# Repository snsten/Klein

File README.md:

# Klein Keyboard

Klein keyboard is a 36 keys, columnar staggered, split keyboard named after [Felix Klein](https://en.wikipedia.org/wiki/Felix_Klein)

---

## Features

- Column Staggered
- Bluetooth compatible with power switch
- Seeed Studio XIAO-BLE / Pro Micro / nice!nano\* / KB2040 / RP2040(boards with Pro Micro pinout) compatible
- Hotswap MX and Choc switches support
- Trackpad support with FPC cable and direct wiring
- Reversible SMD and through hole diode footprint

> \* nice!nano firmware not available at the moment.

## Versions

Supports multiple options of micro controller and sensors.

| Features Supported                       | Microcontroller | Firmware available                         | Wired | Wireless |
| ---------------------------------------- | --------------- | ------------------------------------------ | ----- | -------- |
| Encoder or OLED                          | XIAO-BLE        | [Yes](https://github.com/snsten/Klein-zmk) |       | Yes      |
| Encoder, OLED, TouchPad, Buzzer, Haptics | Pro Micro       | [Yes](https://github.com/snsten/Klein-qmk) | Yes   |          |
| Encoder, OLED, TouchPad, Buzzer, Haptics | KB2040/RP2040   | [Yes](https://github.com/snsten/Klein-qmk) | Yes   |          |
| Encoder and OLED                         | nice!nano       | No (Planned)                               |       | Yes      |

Broadly divided in two types:

### Wireless

- Can be made with Seeed Studio XIAO-BLE
- Supports either rotary encoder or OLED
- Battery connectors JST and THT

Wireless touchpad is currently not supported in ZMK.

### Wired

- With any Pro Micro based boards
  - Can support encoders, OLED, Touchpad, Buzzer and Haptics

---

### Keyboard Images

PCB with both Choc and MX switches

Low Profile Choc version

MX version

---

## Repo Layout and Files

```
.
├── BOM
│   ├── BOM-3235-SEEED.csv         <- BOM
│   └── ibom.html
├── Case
│   └── *.stl                      <- Case stl Files
│   └── Prototype                  <- FreeCad project files (Not tested)
│       └── SwitchPlateFR4         <- SwitchPlate PCB files (Not tested)
├── docs
│   └── images
├── Logo
├── PCB
└── README.md
```

## BOM

It is available in BOM directory as csv file and [interactive HTML BOM](https://htmlpreview.github.io/?https://github.com/snsten/Klein/blob/main/BOM/ibom.html)

## Build Guide

- Wired build [guide](https://github.com/snsten/Klein/blob/main/docs/buildguides/buildguide_wired.md)
- Wireless build [guide](https://github.com/snsten/Klein/blob/main/docs/buildguides/buildguide_wireless.md)

## Todo

- Add Build Guide
- Add Touchpad related 3D Models
- Software support for Touchpad/OLED

## Firmware

- [ZMK shield](https://github.com/snsten/Klein-zmk) for Klein with rotary encoder support.
- [QMK Firmware](https://github.com/snsten/Klein-qmk) for Pro Micro with touchpad support.

## Refrences

These projects inspired and helped in making Klein:

- [Lily58](https://github.com/kata0510/Lily58) (Hotswap Footprints)
- [Dilemma](https://github.com/Bastardkb/dilemma) (Trackpad Mount, Design)
- [KLOR](https://github.com/GEIGEIGEIST/KLOR) (Haptics Footprints, Design)
- [Claw44](https://github.com/yfuku/claw44) (Design)

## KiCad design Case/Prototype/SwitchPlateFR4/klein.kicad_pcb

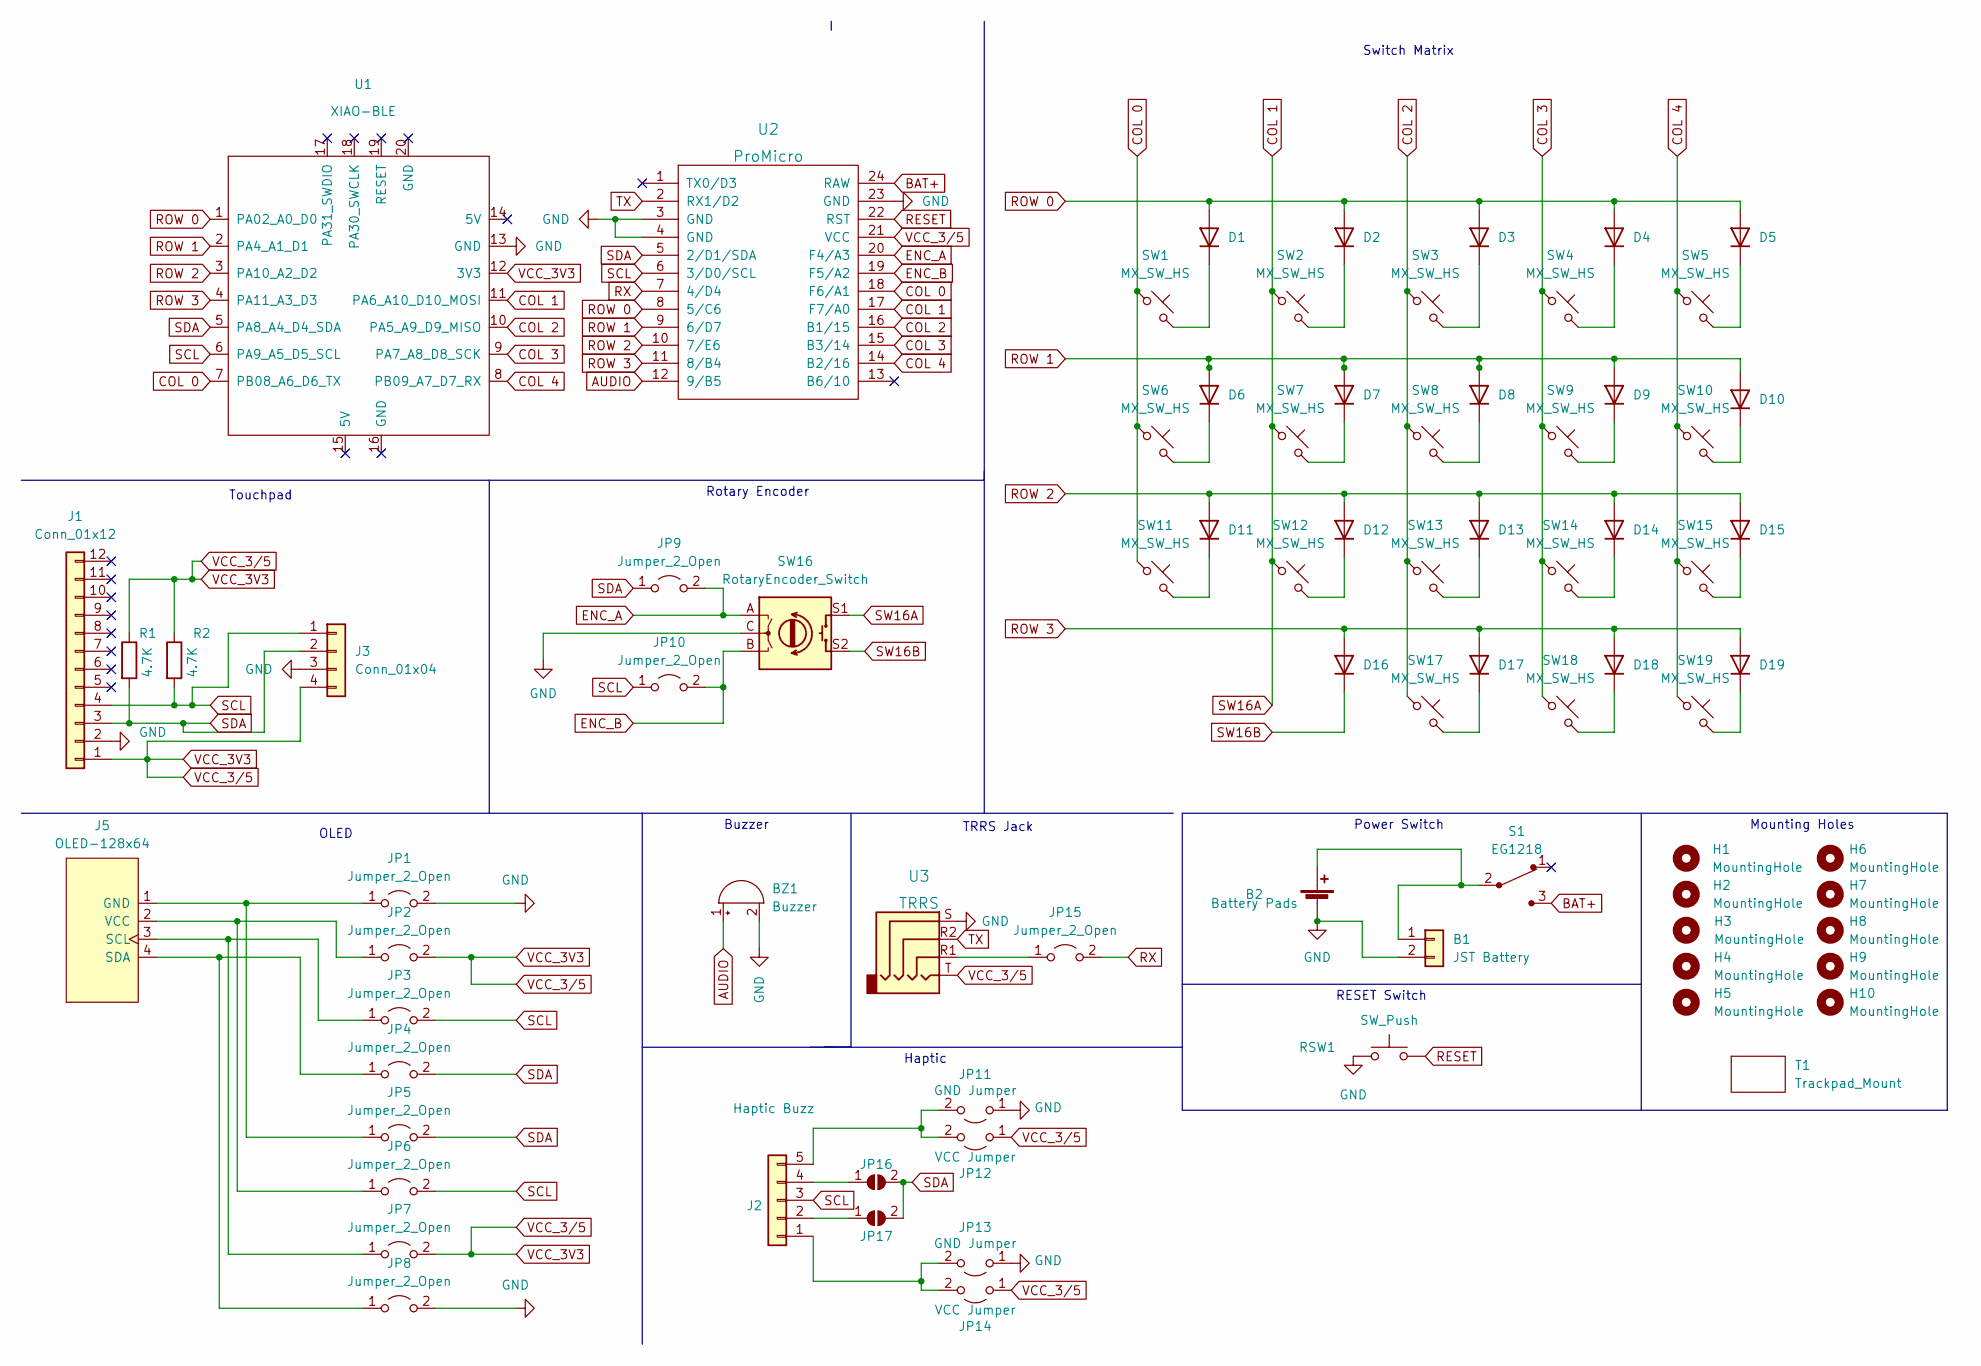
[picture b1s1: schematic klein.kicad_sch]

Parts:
B1: JST Battery; JST_PH_reversible
B2: Battery Pads; SolderWire-0.5sqmm_1x02_P4.8mm_D0.9mm_OD2.3mm
BZ1: Buzzer; Buzzer_Mallory_AST1109MLTRQ_reversible
D1, D2, D3, D4, D5, D6, D7, D8, D9, D10, D11, D12, D13, D14, D15, D16, D17, D18, D19: DIODE; D3_TH_SMD
H1, H2, H4, H5, H6, H8: MountingHole; MountingHole_3.2mm_M3_ISO7380_Pad
H3: MountingHole; MountingHole_3.2mm_M3
H7: MountingHole; MountingHole_2.2mm_M2
H9, H10: MountingHole; MountingHole_2.2mm_M2_ISO7380_Pad
J1: Conn_01x12; Hirose_FH12-12S-0.5SH_1x12-1MP_P0.50mm_Horizontal
J2: Haptic Buzz; Pimoroni Haptic Buzz DRV2605L Driver
J3: Conn_01x04; SolderWire-0.1sqmm_1x04_P3.6mm_D0.4mm_OD1mm
J5: OLED-128x64
JP1, JP2, JP3, JP4, JP5, JP6, JP7, JP8, JP15: Jumper_2_Open; SolderJumper-2_P1.3mm_Open_RoundedPad1.0x1.5mm
JP9, JP10: Jumper_2_Open; SolderJumper-2_P1.3mm_Open_Pad1.0x1.5mm
JP11, JP13: GND Jumper; SolderJumper-2_P1.3mm_Open_Pad1.0x1.5mm
JP12, JP14: VCC Jumper; SolderJumper-2_P1.3mm_Open_Pad1.0x1.5mm
JP16, JP17: SolderJumper_2_Open; SolderJumper-2_P1.3mm_Open_Pad1.0x1.5mm
R1, R2: 4.7K; RESISTOR
RSW1: SW_Push; SW_Push_1P1T-MP_NO_Horizontal_Alps_SKRTLAE010_both_sides
S1: EG1218; RevSlideSwitch; MPN EG1218; Digi-Key_PN EG1903-ND
SW1, SW2, SW3, SW4, SW5, SW6, SW7, SW8, SW9, SW10, SW11, SW12, SW13, SW14, SW15, SW17, SW18, SW19: MX_SW_HS; MX_Choc_Hotswap_Mod
SW16: RotaryEncoder_Switch; MX-1U-EC11_Switch
T1: Trackpad_Mount; Trackpad Mount
U1: XIAO-BLE
U2: ProMicro; ProMicro_rev2
U3: TRRS; MJ-4PP-9

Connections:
AUDIO: BZ1.1 (-), U2.12 (9/B5)
BAT+: S1.3, U2.24 (RAW)
COL 0: SW1.1, SW6.1, SW11.1, U1.7 (PB08_A6_D6_TX), U2.18 (F6/A1)
COL 1: SW2.1, SW7.1, SW12.1, SW16.S1, U1.11 (PA6_A10_D10_MOSI), U2.17 (F7/A0)
COL 2: SW3.1, SW8.1, SW13.1, SW17.1, U1.10 (PA5_A9_D9_MISO), U2.16 (B1/15)
COL 3: SW4.1, SW9.1, SW14.1, SW18.1, U1.9 (PA7_A8_D8_SCK), U2.15 (B3/14)
COL 4: SW5.1, SW10.1, SW15.1, SW19.1, U1.8 (PB09_A7_D7_RX), U2.14 (B2/16)
ENC_A: JP9.2 (B), SW16.A, U2.20 (F4/A3)
ENC_B: JP10.2 (B), SW16.B, U2.19 (F5/A2)
GND: B1.2, B2.2 (-), BZ1.2 (+), J1.2, J3.3, JP1.2 (B), JP8.2 (B), JP11.1 (A), JP13.1 (A), RSW1.1, SW16.C, U1.13 (GND), U2.3 (GND), U2.4 (GND), U2.23 (GND), U3.S
unnamed: B1.1, B2.1 (+), S1.2
unnamed: D1.1 (K), SW1.2
unnamed: D2.1 (K), SW2.2
unnamed: D3.1 (K), SW3.2
unnamed: D4.1 (K), SW4.2
unnamed: D5.1 (K), SW5.2
unnamed: D6.1 (K), SW6.2
unnamed: D7.1 (K), SW7.2
unnamed: D8.1 (K), SW8.2
unnamed: D9.1 (K), SW9.2
unnamed: D10.1 (K), SW10.2
unnamed: D11.1 (K), SW11.2
unnamed: D12.1 (K), SW12.2
unnamed: D13.1 (K), SW13.2
unnamed: D14.1 (K), SW14.2
unnamed: D15.1 (K), SW15.2
unnamed: D17.1 (K), SW17.2
unnamed: D18.1 (K), SW18.2
unnamed: D19.1 (K), SW19.2
unnamed: J2.1, JP13.2 (B), JP14.2 (B)
unnamed: J2.2, JP17.1 (A)
unnamed: J2.4, JP16.1 (A)
unnamed: J2.5, JP11.2 (B), JP12.2 (B)
unnamed: J5.1 (GND), JP1.1 (A), JP5.1 (A)
unnamed: J5.2 (VCC), JP2.1 (A), JP6.1 (A)
unnamed: J5.3 (SCL), JP3.1 (A), JP7.1 (A)
unnamed: J5.4 (SDA), JP4.1 (A), JP8.1 (A)
unnamed: JP15.1 (A), U3.R1
RESET: RSW1.2, U2.22 (RST)
ROW 0: D1.2 (A), D2.2 (A), D3.2 (A), D4.2 (A), D5.2 (A), U1.1 (PA02_A0_D0), U2.8 (5/C6)
ROW 1: D6.2 (A), D7.2 (A), D8.2 (A), D9.2 (A), D10.2 (A), U1.2 (PA4_A1_D1), U2.9 (6/D7)
ROW 2: D11.2 (A), D12.2 (A), D13.2 (A), D14.2 (A), D15.2 (A), U1.3 (PA10_A2_D2), U2.10 (7/E6)
ROW 3: D16.2 (A), D17.2 (A), D18.2 (A), D19.2 (A), U1.4 (PA11_A3_D3), U2.11 (8/B4)
RX: JP15.2 (B), U2.7 (4/D4)
SCL: J1.4, J2.3, J3.1, JP3.2 (B), JP6.2 (B), JP10.1 (A), R2.2, U1.6 (PA9_A5_D5_SCL), U2.6 (3/D0/SCL)
SDA: J1.3, J3.2, JP4.2 (B), JP5.2 (B), JP9.1 (A), JP16.2 (B), JP17.2 (B), R1.2, U1.5 (PA8_A4_D4_SDA), U2.5 (2/D1/SDA)
SW16B: D16.1 (K), SW16.S2
TX: U2.2 (RX1/D2), U3.R2
VCC_3V3: J1.1, J3.4, JP2.2 (B), JP7.2 (B), JP12.1 (A), JP14.1 (A), R1.1, R2.1, U1.12 (3V3), U2.21 (VCC), U3.T

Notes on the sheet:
Switch Matrix
OLED
Rotary Encoder
Touchpad
Haptic
Power Switch
Buzzer
TRRS Jack
RESET Switch
Mounting Holes

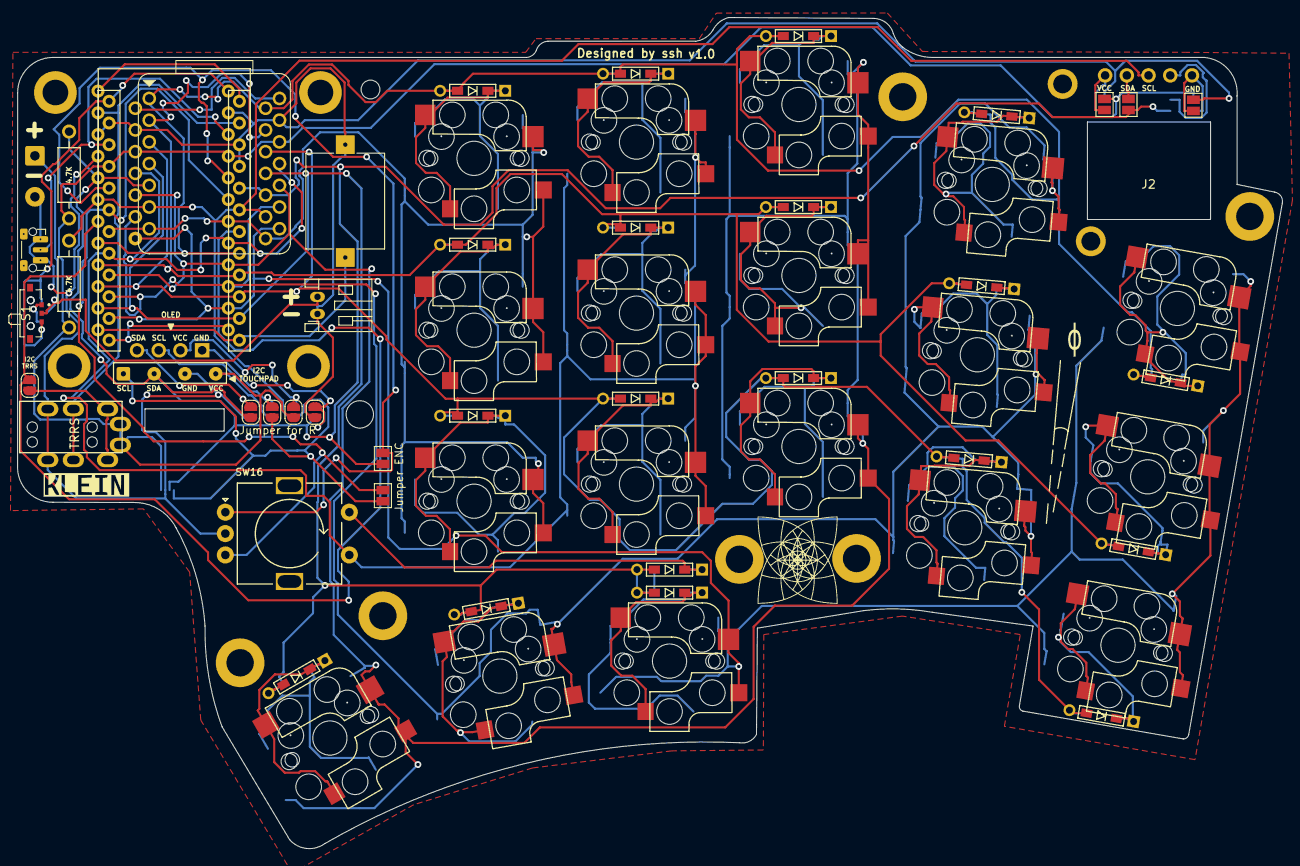
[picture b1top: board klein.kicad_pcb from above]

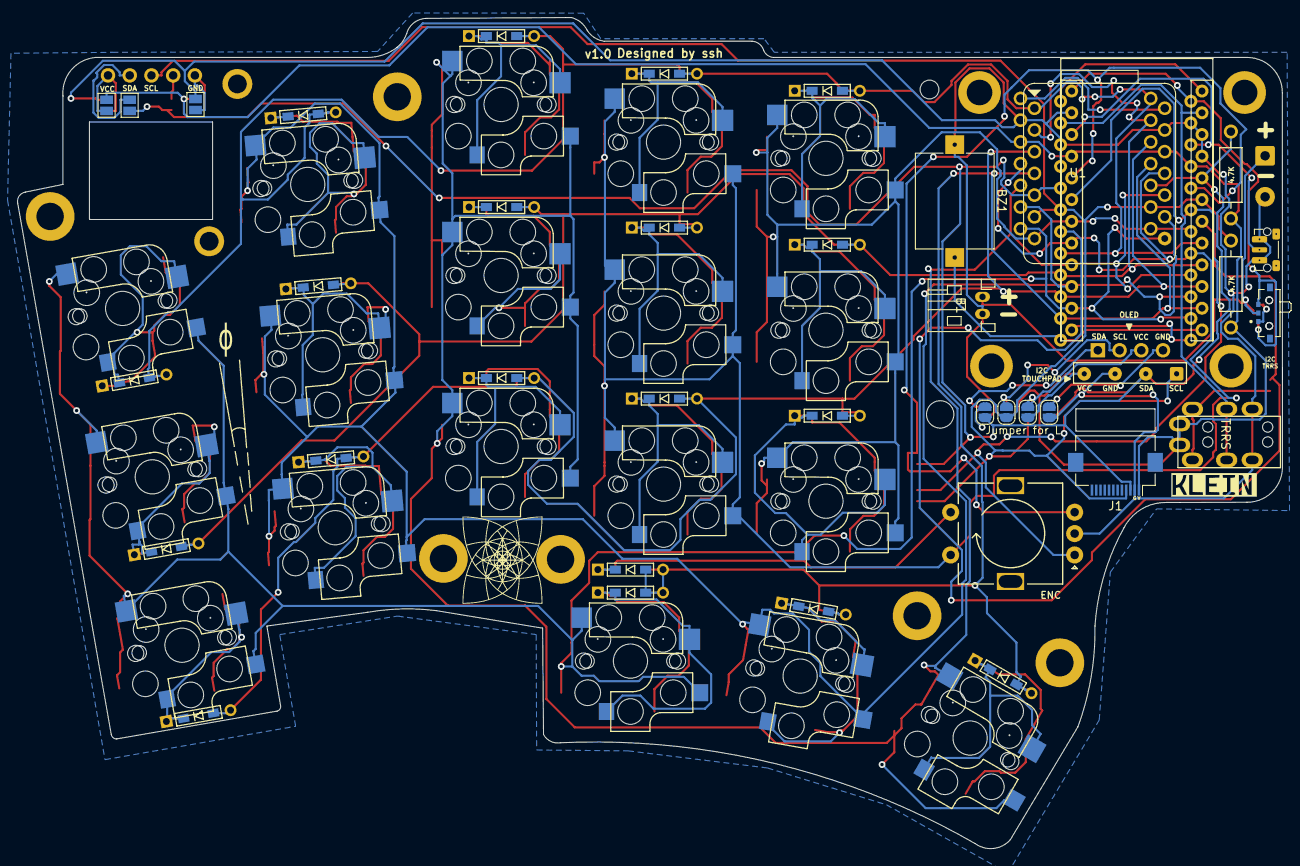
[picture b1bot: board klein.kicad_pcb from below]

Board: 2 copper layers, 147.9 x 97.2 mm, 84 parts (49 on the bottom side), 49 nets.

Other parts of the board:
G3, G4: LOGO; klein
G33, G34: LOGO; klein_small

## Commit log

2022-10-23 Fix the IBOM link
2022-10-24 Added BOM csv file
2022-10-24 Update BOM-3235-SEEED.csv
    Changed "RS1" to "RSW1" to match the interactive BOM.
2022-10-25 Updated case files
2022-10-31 Fix PCB Encoder Routes (Typo in Schematic) and IBOM project name fix
2022-10-31 Removed Gerbers due to missing router for Encoders in Pro Micro based controllers
2022-11-10 Fix OLED silk screen text
2022-11-15 Updated readme for better feature description
2022-11-18 Fix JST battery connector B1 part difference in BOM and PCB
2022-11-19 Added FreeCad Case design files
2022-11-20 Added initial wireless build guide
2022-11-20 Minor change in wireless build guide and Readme
2022-11-20 Added battery info in wireless build guide
2022-12-18 Added qmk firmware link for KB2040 in README
2022-12-19 Wired build guide added
2022-12-19 Fix firmware link in wired build guide
2022-12-19 Updated case design with better fit, support structures and initial trackpad mount design
2022-12-24 Fix diode clearance on last column
2023-01-07 Added wired build guide link in readme
2023-02-19 Removed TRRS jumper
2023-02-19 Added Switchplate PCB files and updated readme
2023-07-23 Added XIAO Cover Plate
    Useful for laser cutting acrylic cover for xiao and an alternative to the 3d printed cover
2023-09-05 Switchplate adapted to fit Mx switches.
    Tested with Elegoo Neptune PLA printer.
